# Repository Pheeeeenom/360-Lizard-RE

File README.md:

<div align="center">
  
</div>

<h1 align="center">The Ultimate Flashing Tool</h1>

<p align="center">
  A "modern" clone to the 360 Lizard. 
</p>

# Why bother cloning this?

Mostly for preservations sake, but it really annoyed me having to deal with Windows 10/11 and driver issues, old LTU pcb's getting stuck on "writing .", JungleFlasher using very suspicious remote execution dll's (I'll be going into the software side later in the docs), the clutter of having to having cables all over the place/pc needing to be open to get access to a SATA plug. List goes on.

# Clone features

* Modernize with USB-C
* Replace the old 27 pin out of production 0.96 SPI 1306 screen with a 30 pin equivalent.
* Removeable screen so it's repairable with little effort

# Original features

* Hardware Flasher with Unlock, Read, Write, Erase, Key Retrieval
* Support all Xbox 360 Drives, Samsung, Hitachi, Benq, Liteon, and Slim Liteon. (yes it also unlock and read keys on the latest 0225)
* Built in support for many PC DVD Sata Drives too
* Support Onboard AES 128 Key Verification
* Several Modes of Operation: Use it with your PC or as stand alone
* Micro SD Card Slot for file storage
* Friendly Navigation Menu with simplified button count
* Multilingual Menu
* Free PC companion Software

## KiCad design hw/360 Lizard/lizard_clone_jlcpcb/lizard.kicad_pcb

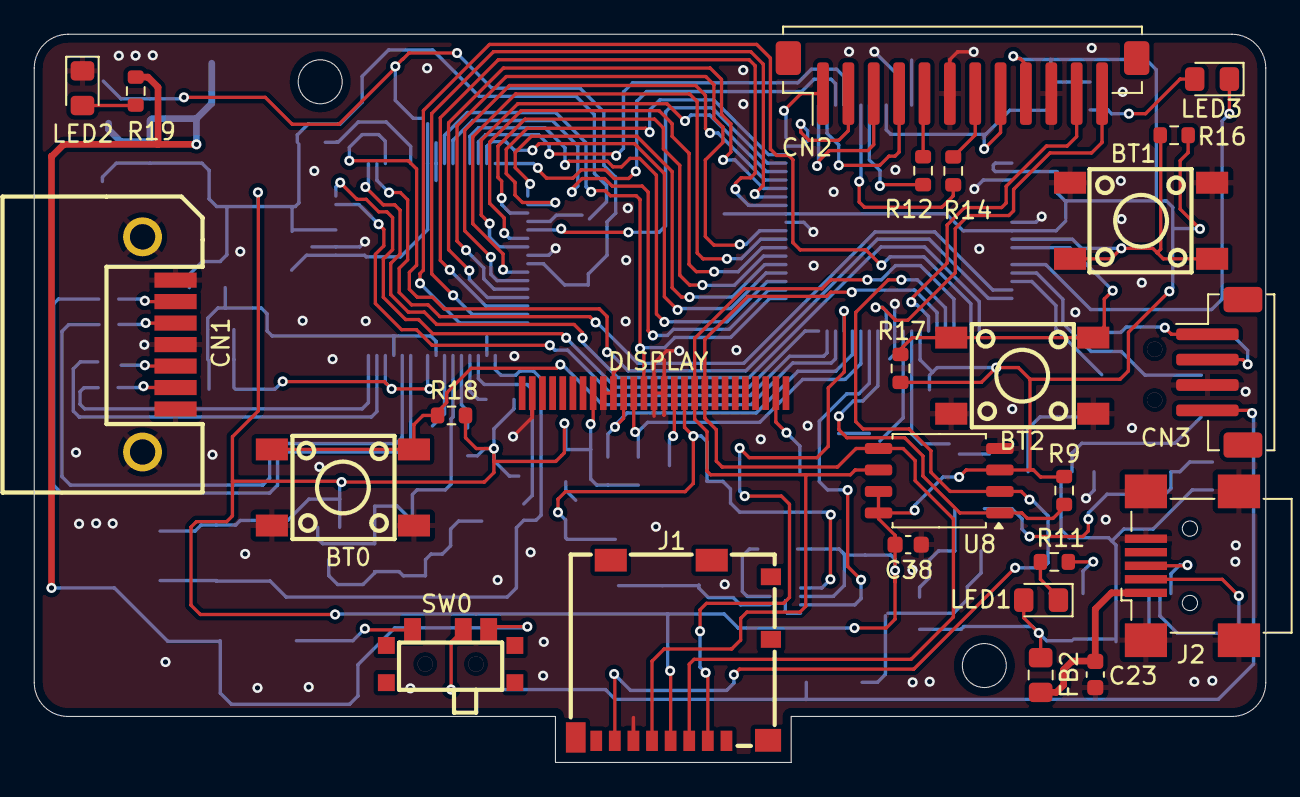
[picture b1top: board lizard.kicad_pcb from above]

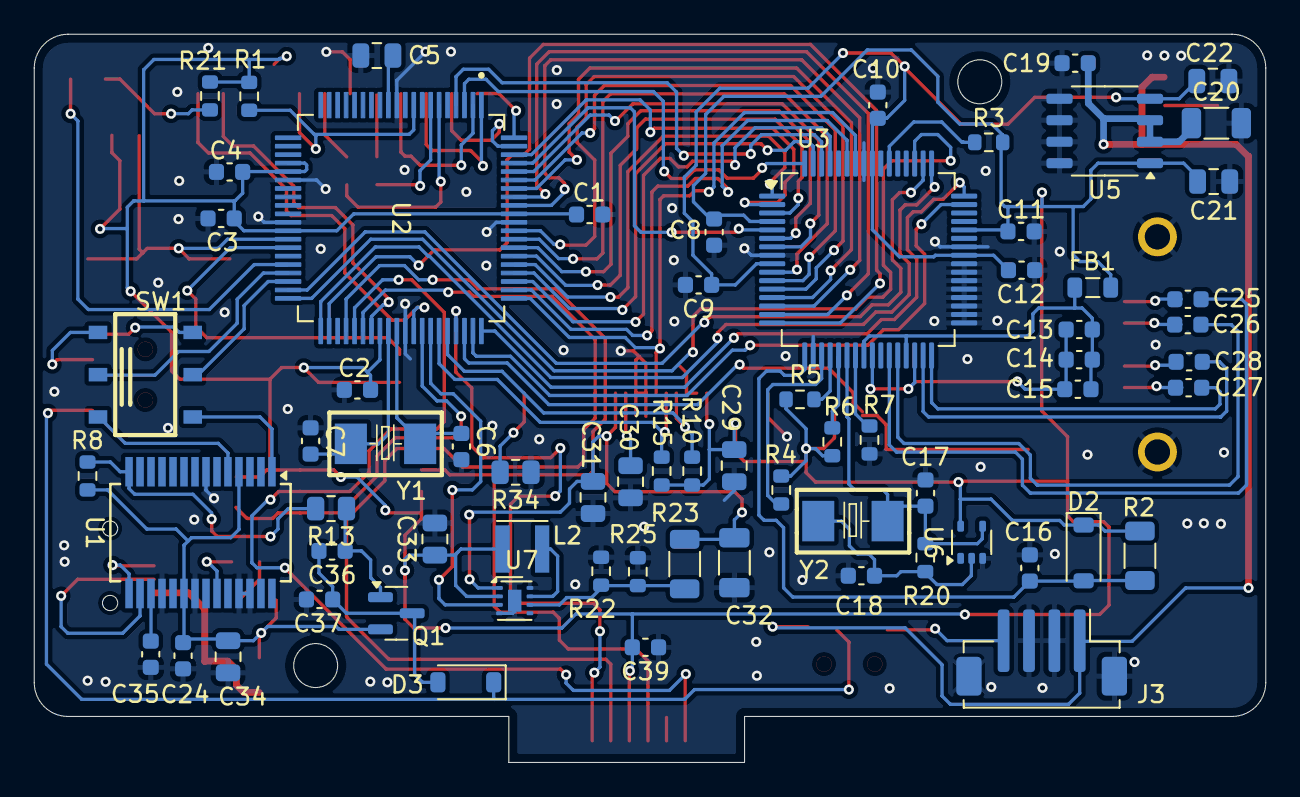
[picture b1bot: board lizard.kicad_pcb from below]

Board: 2 copper layers, 72.8 x 43.1 mm, 94 parts (69 on the bottom side), 97 nets.

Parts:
BT0, BT1, BT2: SW_Push; KEY-SMD_4P-L6.0-W6.0-P4.50-LS9.0
C1, C2, C3, C4, C8, C9, C10, C11, C12, C13, C14, C15, C19, C24, C35, C36, C37, C38, C39: 100nF; C_0603_1608Metric
C5, C21, C22: 10uF; C_0805_2012Metric
C6, C7, C17, C18: 24pF; C_0603_1608Metric
C16: 1uF; C_0603_1608Metric
C20, C32: 10uF; C_1206_3216Metric
C23: 10nF; C_0603_1608Metric
C25, C26, C27, C28: 47nF; C_0603_1608Metric
C29, C30, C31, C34: 5uF; C_0805_2012Metric
C33: 2.7uF; C_0805_2012Metric
CN1: SATA; CONN-SMD_SATA-401-M07S1BY-A
CN2: Conn_01x12_Pin; JST_ZH_B12B-ZR-SM4-TF_1x12-1MP_P1.50mm_Vertical
CN3: Conn_01x04_Pin; JST_ZH_B4B-ZR-SM4-TF_1x04-1MP_P1.50mm_Vertical
D2: 1N4148W; D_SOD-123
D3: MBR0520; D_SOD-123
DISPLAY: OLED-128O064D
FB1: 330nH; L_0805_2012Metric
FB2: 330nH; L_0805_2012Metric_Pad1.15x1.40mm_HandSolder
J1: Micro_SD_Card; SIM-SMD_8P-1040310811
J2: USB_B_Mini; USB_Mini-B_Wuerth_65100516121_Horizontal
J3: Conn_01x04_Pin; JST_ZH_B4B-ZR-SM4-TF_1x04-1MP_P1.50mm_Vertical
L2: 10uH; L_Wurth_WE-LQSH-3012
LED1: BLUE; LED_0805_2012Metric_Pad1.15x1.40mm_HandSolder
LED2: GREEN; LED_0805_2012Metric_Pad1.15x1.40mm_HandSolder
LED3: RED; LED_0805_2012Metric_Pad1.15x1.40mm_HandSolder
Q1: AO3401A; SOT-23
R1, R3, R4, R5, R6, R8, R9, R10, R15, R16, R17, R18, R22, R25: 10k; R_0603_1608Metric
R2, R23: 31.6k; R_1206_3216Metric
R7: 12k; R_0603_1608Metric
R11, R12, R14: 110; R_0603_1608Metric
R13: 1k; R_0805_2012Metric
R19, R21: 270; R_0603_1608Metric
R20: 1M; R_0603_1608Metric
R34: 910k; R_0805_2012Metric
SW0: SK-3296S-01-L1; SW-SMD_3P-P1.50_L2.7-W6.6
SW1: MSS22C02KG10-B; SW-SMD_6P-L7.2-W3.6-P2.50-TL
U1: FT232RL; SSOP-28_5.3x10.2mm_P0.65mm
U2: PIC18F87J11T-I_PT; QFP50P1400X1400X120-80N
U3: LQFP-64_10x10mm_P0.5mm
U5: AP1121B; SSOP-8_3.9x5.05mm_P1.27mm
U6: 74LVC1G04; SOT-353_SC-70-5
U7: MIC2290; Micrel_MLF-8-1EP_2x2mm_P0.5mm_EP0.8x1.3mm_ThermalVias
U8: W25Q32JVSS; SOIC-8_5.3x5.3mm_P1.27mm
Y1: 10MHz; OSC-SMD_L5.0-W3.2
Y2: 20MHz; OSC-SMD_L5.0-W3.2

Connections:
+1V8: C9.1, C10.1, C12.2, C22.2, U3.9, U3.41, U3.56, U5.4 (VOUT2)
+3V3: C1.2, C2.1, C3.1, C4.1, C8.2, C11.2, C21.2, C29.2, C33.1, C38.1, C39.2, CN2.9, D2.1 (K), DISPLAY.8 (VDD), FB1.1, J1.4 (VDD), L2.2, R1.1, R2.2, R3.2, R4.2, R5.2, R6.1, R9.2, R10.1, R15.2, R16.2, R17.2, R18.2, R21.1, U2.24 (ENVREG), U2.25 (AVDD), U2.32 (VDD), U2.48 (VDD), U2.71 (VDD), U3.4, U3.44, U5.1 (VOUT1), U6.5 (VCC), U7.2 (VIN), U8.3 (~WP/IO_{2}), U8.7 (~HOLD/~RESET/IO_{3}), U8.8 (VCC)
+3V3_SATA: C13.1, C14.1, C15.1, FB1.2, U3.24, U3.29
+5V: C19.1, C20.1, J3.1, R19.2, SW0.3, U5.2 (VIN), U5.3 (VIN)
/Lizard main ICs/3V3OUT: C35.2, U1.17 (3V3OUT)
/Lizard main ICs/OSC1: C7.2, U2.49 (OSC1/CLKI/RA7), Y1.2 (OSC2)
/Lizard main ICs/OSC2: C6.2, U2.50 (OSC2/CLKO/RA6), Y1.1 (OSC1)
/Lizard peripherals/IREF: DISPLAY.26 (IREF), R34.2
/Lizard peripherals/SATA_A+: C25.2, CN1.2
/Lizard peripherals/SATA_A-: C26.2, CN1.3
/Lizard peripherals/SATA_B+: C27.2, CN1.6
/Lizard peripherals/SATA_B-: C28.2, CN1.5
/Lizard peripherals/VCOMH: C30.2, DISPLAY.16 (VCOMH)
CBUS0: R11.2, U1.23 (CBUS0)
CBUS3: R8.1, R13.2, U1.14 (CBUS3)
EXT_5V: CN3.4, D3.1 (K), SW0.2
EXT_5V_J3: J3.4, SW0.1
EXT_RXD: CN3.2, SW1.4
EXT_TXD: CN3.1, SW1.1
FLASH_nCS: R9.1, U2.53 (RB5/KBI1/PMA0), U8.1 (~CS)
GND: BT0.1, BT0.2, BT1.1, BT1.2, BT2.1, BT2.2, C1.1, C2.2, C3.2, C4.2, C5.2, C6.1, C7.1, C8.1, C9.2, C10.2, C11.1, C12.1, C16.2, C17.2, C18.2, C19.2, C20.2, C21.1, C22.1, C23.1, C24.1, C29.1, C30.1, C31.1, C32.1, C33.2, C34.1, C35.1, C37.1, C38.2, C39.1, CN1.1, CN1.4, CN1.7, CN1.8, CN1.9, CN2.6, CN2.10, CN3.3, DISPLAY.2 (VSS), DISPLAY.9 (BS1), DISPLAY.10 (BS2), DISPLAY.14 (R/~W), DISPLAY.15 (E/~RD), J1.6 (VSS), J2.5 (GND), J2.6 (Shield), J3.2, J3.3, J3.5 (MP), LED2.1 (K), R7.1, R22.2, R25.1, R34.1, U1.7 (GND), U1.18 (GND), U1.21 (GND), U1.25 (AGND), U1.26 (TEST), U2.11 (VSS), U2.26 (AVSS), U2.31 (VSS), U2.51 (VSS), U2.70 (VSS), U3.8, U3.18, U3.33, U3.34, U3.35, U3.36, U3.37, U3.38, U3.39, U3.40, U3.42, U3.57, U5.5 (GND), U5.6 (GND), U5.7 (GND), U5.8 (GND), U6.3 (GND), U7.4 (AGND), U7.8 (PGND), U7.9 (EP_GND), U8.4 (GND)
MRV_23: R7.2, U3.23
MRV_27: C25.1, U3.27
MRV_28: C26.1, U3.28
MRV_31: C28.1, U3.31
MRV_32: C27.1, U3.32
MRV_OSC_IN: C17.1, R20.2, U3.22, U6.4, Y2.1 (OSC1)
unnamed: CN2.5, R12.2
unnamed: CN2.7, R14.1
unnamed: C16.1, D2.2 (A), R2.1, U3.17
unnamed: C36.2, C37.2, D3.2 (A), Q1.3 (D)
unnamed: C23.2, FB2.1, J2.1 (VBUS)
unnamed: LED1.1 (K), R11.1
unnamed: LED2.2 (A), R19.1
unnamed: LED3.2 (A), R21.2
unnamed: C36.1, Q1.1 (G), R13.1
unnamed: R3.1, U3.54
unnamed: R4.1, U3.19
unnamed: R5.1, U3.20
unnamed: R6.2, U3.21
unnamed: C5.1, U2.12 (VDDCORE/VCAP)
unnamed: R22.1, R23.1, R25.2, U7.6 (FB)
unnamed: L2.1, U7.7 (SW)
unnamed: C18.1, R20.1, U6.2, Y2.2 (OSC2)
PGC: CN2.12, U2.52 (RB6/KBI2/PGC)
PGD: CN2.11, U2.47 (RB7/KBI3/PGD)
RA4: BT2.3 (K), BT2.4 (A), R17.1, U2.34 (RA4/PMD5/T0CKI)
RA5: BT1.3 (K), BT1.4 (A), R16.1, U2.33 (RA5/PMD4/AN4)
RB0: BT0.3 (K), BT0.4 (A), R18.1, U2.58 (RB0/INT0/FLT0)
RB2: DISPLAY.11 (~CS), R10.2, U2.56 (RB2/INT2/PMA3)
RB3: DISPLAY.12 (~RES), R15.1, U2.55 (RB3/INT3/PMA2/ECCP2/P2A)
RB4: U2.54 (RB4/KBI0/PMA1), U7.3 (EN)
RC0: LED3.1 (K), U2.36 (RC0/T1OSO/T13CKI)
RC6: SW1.5, U2.37 (RC6/TX1/CK1)
RC7: SW1.2, U2.38 (RC7/RX1/DT1)
RD0: U2.72 (RD0/AD0/PMD0), U3.14
RD1: U2.69 (RD1/AD1/PMD1), U3.12
RD2: U2.68 (RD2/AD2/PMD2), U3.10
RD3: U2.67 (RD3/AD3/PMD3), U3.6
RD4: U2.66 (RD4/AD4/PMD4/SDO2), U3.3
RD5: U2.65 (RD5/AD5/PMD5/SDI2/SDA2), U3.1
RD6: U2.64 (RD6/AD6/PMD6/SCK2/SCL2), U3.63
RD7: U2.63 (RD7/AD7/PMD7/~SS2), U3.61
RE0: U2.4 (RE0/AD8/PMRD/P2D), U3.62
RE1: U2.3 (RE1/AD9/PMWR/P2C), U3.64
RE2: U2.78 (RE2/AD10/PMBE/P2B), U3.2
RE3: U2.77 (RE3/AD11/PMA13/P3C/REFO), U3.5
RE4: U2.76 (RE4/AD12/PMA12/P3B), U3.7
RE5: U2.75 (RE5/AD13/PMA11/P1C), U3.11
RE6: U2.74 (RE6/AD14/PMA10/P1B), U3.13
RE7: U2.73 (RE7/AD15/PMA9/ECCP2/P2A), U3.15
RG1: R14.2, U2.6 (RG1/PMA7/TX2/CK2)
RG2: R12.1, U2.7 (RG2/PMA6/RX2/DT2)
RH0: CN2.2, U2.79 (RH0/A16)
RH1: CN2.1, U2.80 (RH1/A17)
RH2: CN2.3, U2.1 (RH2/A18/PMD7)
RH3: CN2.4, U2.2 (RH3/A19/PMD6)
RJ0: U2.62 (RJ0/ALE), U3.59
RJ1: DISPLAY.13 (D/~C), U2.61 (RJ1/~OE), U3.58
RJ2: U2.60 (RJ2/~WRL), U3.48
RJ3: U2.59 (RJ3/~WRH), U3.47
RJ4: U2.39 (RJ4/BA0), U3.50
RJ5: U2.40 (RJ5/~CE), U3.51
RJ6: U2.41 (RJ6/~LB), U3.49
RJ7: U2.42 (RJ7/~UB), U3.16
RXD: SW1.6, U1.5 (RXD)
SATA_GND: C13.2, C14.2, C15.2, U3.25, U3.30
SD_DAT3: J1.2 (DAT3/CD), U2.57 (RB1/INT1/PMA4)
SPI_CLK: DISPLAY.18 (D0), J1.5 (CLK), U2.44 (RC3/SCK1/SCL1), U8.6 (CLK)
SPI_MISO: DISPLAY.19 (D1), J1.3 (CMD), U2.46 (RC5/SDO1), U8.5 (DI/IO_{0})
SPI_MOSI: J1.7 (DAT0), U2.45 (RC4/SDI1/SDA1), U8.2 (DO/IO_{1})
TXD: SW1.3, U1.1 (TXD)
USB_DM: J2.2 (D-), U1.16 (USBD-)
USB_DP: J2.3 (D+), U1.15 (USBD+)
VPANEL: C31.2, C32.2, DISPLAY.17 (VCC), R23.2, U7.1 (OUT)
VUSB: C24.2, C34.2, FB2.2, LED1.2 (A), Q1.2 (S), R8.2, U1.4 (VCCIO), U1.20 (VCC)
/MCLR: CN2.8, R1.2, U2.9 (~MCLR)

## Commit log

2025-07-18 initial upload
2025-07-18 organization
2025-07-21 schematic and updater
2025-07-24 KiCad Project
2025-08-08 Finalized clone
2025-08-31 CK3 USB PD
2025-09-21 Updated USB PD CK3
2025-10-06 cleanup
2025-10-13 Create LICENSE
2025-10-21 add some files
2025-10-21 truncate to first 256kb for actual gui data
2025-11-06 Board bring up instructions
2025-11-06 Update Programming.md with links to firmware files
2025-11-11 Add 1.33 SPI
2025-11-11 correct versioning
2026-01-18 Toolbox barebones
2026-01-18 oops
2026-01-19 Update firmware_parser.c
    Add Samsung parsing / LITE-ON D2S and 9504/0272 D4S parsing (requires graph.dll from original toolbox)
